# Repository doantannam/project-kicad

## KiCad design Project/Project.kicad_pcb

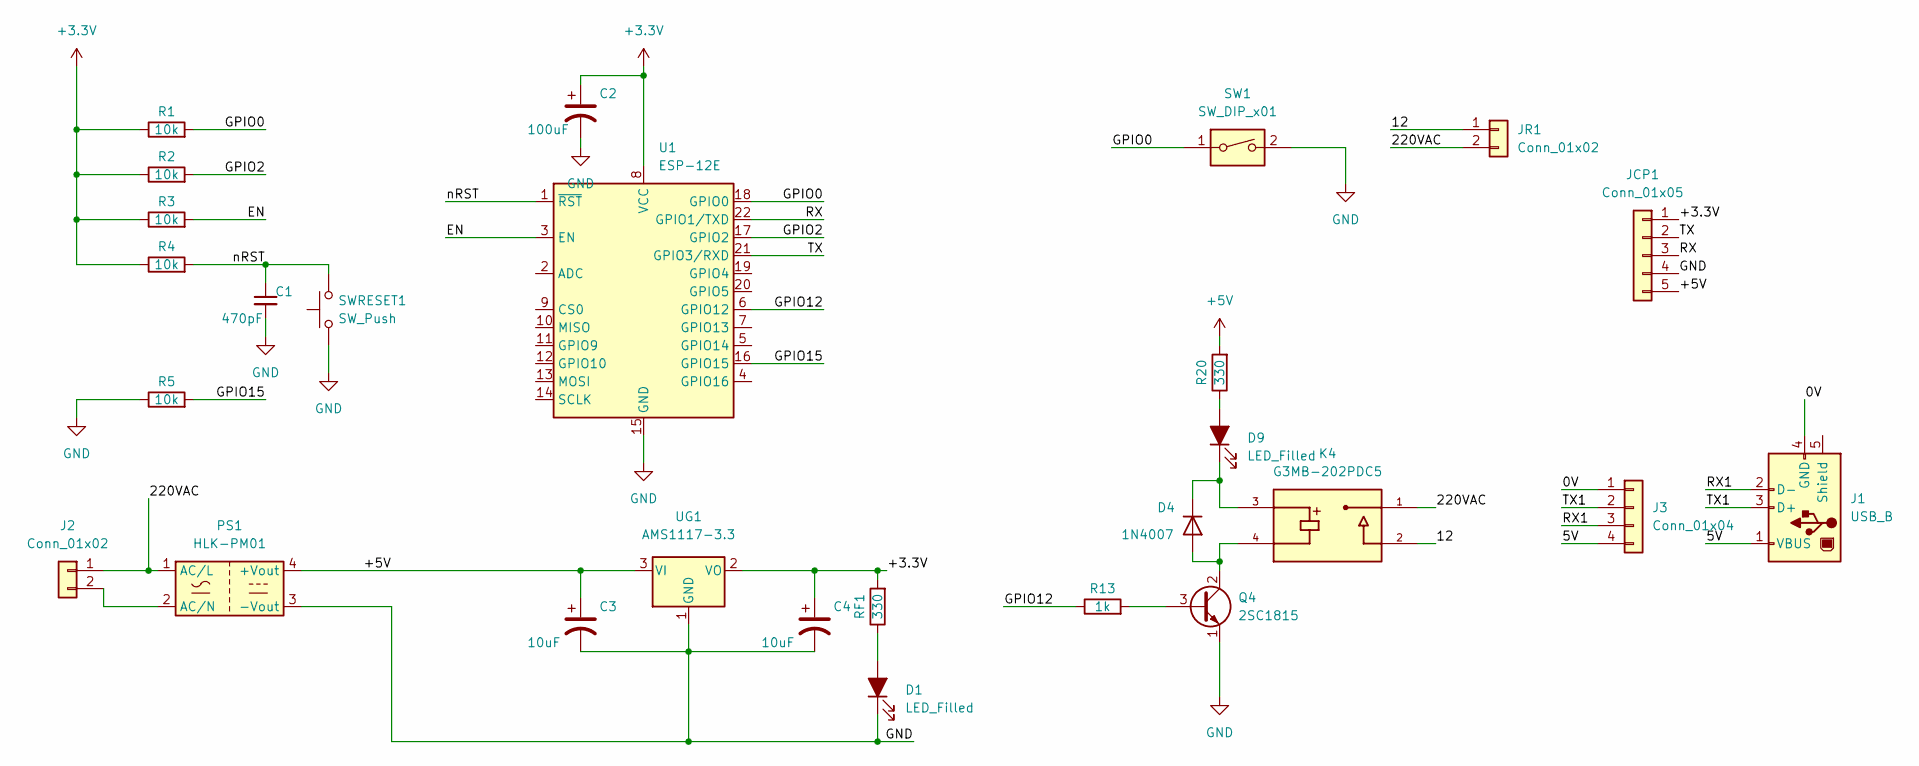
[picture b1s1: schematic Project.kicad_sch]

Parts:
C1: 470pF; C_Disc_D5.0mm_W2.5mm_P5.00mm
C2: 100uF; CP_Radial_D5.0mm_P2.50mm
C3, C4: 10uF; CP_Radial_D5.0mm_P2.50mm
D1, D9: LED_Filled; LED_D3.0mm
D4: 1N4007; D_DO-41_SOD81_P10.16mm_Horizontal
J1: USB_B; USB_B_Lumberg_2411_02_Horizontal
J2: Conn_01x02; PhoenixContact_MC_1,5_2-G-3.81_1x02_P3.81mm_Horizontal
J3: Conn_01x04; PinSocket_1x04_P2.54mm_Vertical
JCP1: Conn_01x05; PinSocket_1x05_P2.54mm_Vertical
JR1: Conn_01x02; PhoenixContact_MC_1,5_2-G-3.81_1x02_P3.81mm_Horizontal
K4: G3MB-202PDC5; RELAY_G3MB-202PDC5; PARTREV J091-E1-1A
PS1: HLK-PM01; Converter_ACDC_HiLink_HLK-PMxx
Q4: 2SC1815; TO-92_Inline
R1, R2, R3, R4, R5: 10k; R_Axial_DIN0207_L6.3mm_D2.5mm_P10.16mm_Horizontal
R13: 1k; R_Axial_DIN0207_L6.3mm_D2.5mm_P10.16mm_Horizontal
R20: 330; R_Axial_DIN0207_L6.3mm_D2.5mm_P10.16mm_Horizontal
RF1: 330; R_Axial_DIN0207_L6.3mm_D2.5mm_P10.16mm_Horizontal
SW1: SW_DIP_x01; SW_DIP_SPSTx01_Slide_9.78x4.72mm_W7.62mm_P2.54mm
SWRESET1: SW_Push; SW_PUSH_6mm
U1: ESP-12E
UG1: AMS1117-3.3; SOT-223-3_TabPin2

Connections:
+3.3V: C2.1, C4.1, JCP1.1, R1.1, R2.1, R3.1, R4.1, RF1.2, U1.8 (VCC), UG1.2 (VO)
+5V: C3.1, JCP1.5, PS1.4 (+Vout), R20.2, UG1.3 (VI)
/0V: J1.4 (GND), J3.1
/5V: J1.1 (VBUS), J3.4
/12: JR1.1, K4.2
/220VAC: J2.1, JR1.2, K4.1, PS1.1 (AC/L)
/EN: R3.2, U1.3 (EN)
/GPIO0: R1.2, SW1.1, U1.18 (GPIO0)
/GPIO2: R2.2, U1.17 (GPIO2)
/GPIO12: R13.1, U1.6 (GPIO12)
/GPIO15: R5.2, U1.16 (GPIO15)
/RX: JCP1.3, U1.22 (GPIO1/TXD)
/RX1: J1.2 (D-), J3.3
/TX: JCP1.2, U1.21 (GPIO3/RXD)
/TX1: J1.3 (D+), J3.2
/nRST: C1.1, R4.2, SWRESET1.2, U1.1 (~RST)
GND: C1.2, C2.2, C3.2, C4.2, D1.1 (K), JCP1.4, PS1.3 (-Vout), Q4.1 (E), R5.1, SW1.2, SWRESET1.1, U1.15 (GND), UG1.1 (GND)
unnamed: D1.2 (A), RF1.1
unnamed: D4.1 (K), D9.1 (K), K4.3
unnamed: D4.2 (A), K4.4, Q4.2 (C)
unnamed: D9.2 (A), R20.1
unnamed: J2.2, PS1.2 (AC/N)
unnamed: Q4.3 (B), R13.2

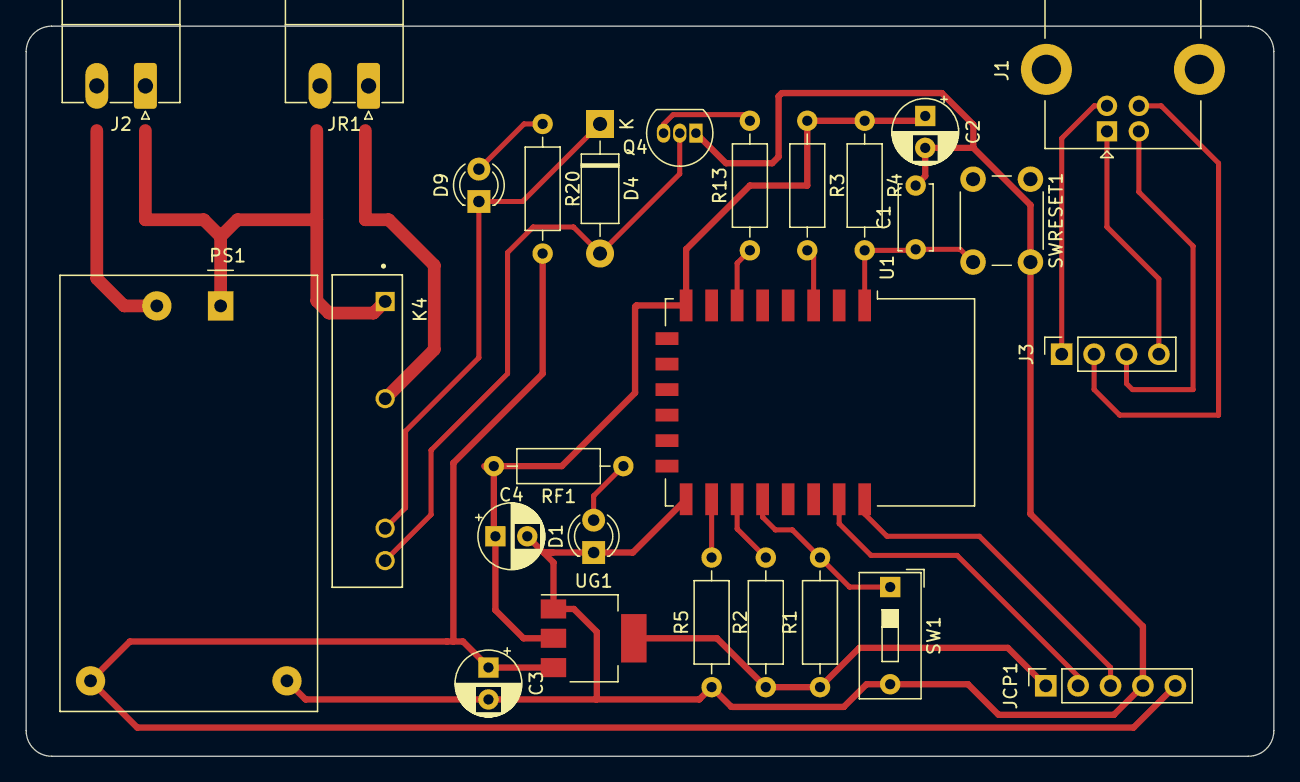
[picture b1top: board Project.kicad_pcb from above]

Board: 2 copper layers, 97.8 x 57.2 mm, 27 parts (0 on the bottom side), 23 nets.

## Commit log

2022-12-05 create kicad
